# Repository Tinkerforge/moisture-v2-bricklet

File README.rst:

Moisture Bricklet 2.0
=====================

**The development of this Bricklet was stopped.**

This repository contains the firmware source code and the hardware design
files. The documentation generator configs can be found at
https://github.com/Tinkerforge/generators

Repository Content
------------------

software/:
 * examples/: Examples for all supported languages
 * build/: Compiled files
 * src/: Source code of firmware
 * Makefile: Makefile to build project

hardware/:
 * Contains KiCad project files and additionally schematics as PDF

datasheets/:
 * Contains datasheets for sensors and complex ICs that are used

Hardware
--------

The hardware is designed with the open source EDA Suite KiCad
(http://www.kicad.org). Before you are able to open the files,
you have to install the Tinkerforge kicad-libraries
(https://github.com/Tinkerforge/kicad-libraries). You can either clone
them directly in hardware/ or clone them in a separate folder and
symlink them into hardware/
(ln -s kicad_path/kicad-libraries project_path/hardware). After that you
can open the .pro file in hardware/ with KiCad and from there view and
modify the schematics and the PCB layout.

Software
--------

If you want to do your own Brick/Bricklet firmware development we highly
recommend that you use our build environment setup script and read the
tutorial (https://www.tinkerforge.com/en/doc/Tutorials/Tutorial_Build_Environment/Tutorial.html).

To compile the C code we recommend you to install the newest GNU Arm Embedded
Toolchain (https://launchpad.net/gcc-arm-embedded/+download).
You also need to install bricklib2 (https://github.com/Tinkerforge/bricklib2).

You can either clone it directly in software/src/ or clone it in a
separate folder and symlink it into software/src/
(ln -s bricklib_path/bricklib2 project_path/software/src/). Finally make sure to
have CMake installed (http://www.cmake.org/cmake/resources/software.html).

After that you can build the firmware by invoking make in software/.
The firmware (.zbin) can then be found in software/build/ and uploaded
with brickv (click button "Flashing" on start screen).

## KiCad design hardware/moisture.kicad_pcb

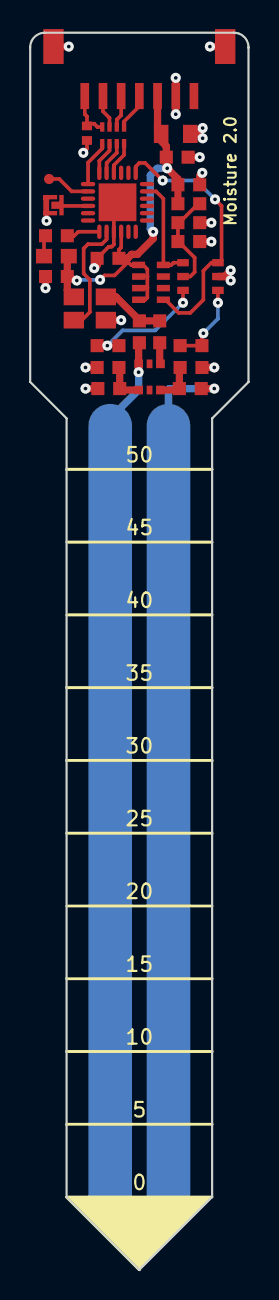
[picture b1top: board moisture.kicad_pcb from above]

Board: 2 copper layers, 15.0 x 85.0 mm, 30 parts (2 on the bottom side), 25 nets.

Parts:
C1: 10uF; C0805
C2: TBD; C0402F
C3, C5, C6: 1uF; C0603F
C4, C7, C8: 100nF; C0603F
C9, C10: TBD; C0603F
D1: blue; D0603E
D2: BAT54TW; SOT363
L1: INDUCT; R0603F
P1: CON-SENSOR2
P2: DEBUG; DEBUG_PAD
P3: BOOT; SolderJumper
Q1: Oscillator; CRYSTAL_3225_4
R1, R3, R6: 1k; R0603F
R2, R5: 68; R0603F
R4, R7: DNP; R0603F
RP1: TBD; 4X0402
RP2: 1k; 4X0603
U1: XMC1XXX24; QFN24-4x4mm-0.5mm
U2: MCP3425; SOT23-6
VAL: WEEE_7mm
VAL#2: CE_5mm

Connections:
CLK-EN: Q1.1, U1.8
GND: C1.1, C2.1, C3.1, C4.2, C5.2, C6.2, C7.2, C8.2, C9.2, C10.2, P1.2, P1.EP, P3.1, Q1.2, R4.1, R7.1, U1.9, U1.EXP, U2.2
unnamed: C2.2, P1.7, RP1.4
unnamed: C6.1, C7.1, L1.2, U2.5
unnamed: C9.1, D2.6, R3.2
unnamed: C10.1, D2.4, R6.2
unnamed: D1.2, R1.2
unnamed: D2.1, R2.1
unnamed: P1.4, RP1.1
unnamed: P1.5, RP1.2
unnamed: P1.6, RP1.3
unnamed: P2.1, U1.2
unnamed: P3.2, U1.4
unnamed: Q1.3, R2.2, R5.2
unnamed: R1.1, U1.7
unnamed: R3.1, R4.2, U2.1
unnamed: R6.1, R7.2, U2.6
S-CLK: RP1.7, U1.23
S-CS: RP1.8, U1.22
S-MISO: RP1.5, U1.1
S-MOSI: RP1.6, U1.24
SCL: RP2.8, U1.19, U2.3
SDA: RP2.5, U1.17, U2.4
SIG: D2.3, R5.1
VCC: C1.2, C3.2, C4.1, C5.1, C8.1, D1.1, L1.1, P1.3, Q1.4, RP2.1, RP2.2, RP2.3, RP2.4, U1.10

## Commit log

2017-07-11 add hardware files for new moisture prototype
2017-08-01 Add 3d information (fam)
2017-08-10 Add datasheets
2017-08-11 Initial software commit
    Current state: Stub implementation of MCP3425 driver that reads ADC value and prints it
2017-08-14 Remove unused logd
2017-08-14 Use fallthrough attribute to not get wrong GCC warning
2017-08-14 Add comment
2018-02-20 Cleanup KiCad libraries config
    Ensure LibDir=kicad-libraries and LibName1=tinkerforge.
    Remove special library.
2018-03-05 change footprints
2018-03-05 Remove unused flash-size define
2018-05-14 Fix kicad-libraries name
2018-06-06 Adapt to bricklib2 callback-value changes to fix wrong length of get-moisture packet
2018-06-28 Fix readme
2018-07-13 Add Makefile with docker support
2018-07-13 Update directory structure and build instructions
2018-07-13 Remove obsolete generate_makefile scripts
2019-12-02 Mark development as stopped
2021-10-25 Update KiCad link
    https://www.kicad.org/blog/2021/10/Avoid-links-to-former-kicad-domain/
2022-07-06 Add license files.

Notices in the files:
hardware/moisture.kicad_pcb:
Licensed under CERN OHL v.1.1
Copyright (©) 2014, B.Nordmeyer
Copyright Tinkerforge GmbH 2014.
This documentation describes Open Hardware and is licensed under the
CERN OHL v. 1.1.
